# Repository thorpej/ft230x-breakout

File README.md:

# A Basic FTDI FT230X Breakout Board

This is a fairly straight-forward breakout board for the FTDI FT230X
USB UART.  The circuit is more-or-less the example bus-powered circuit
in the FT230X data sheet, and all of the I/O pins are simply brought
out to pin headers.  You can point them down for inserting into a breadboard,
or you can point them up for connecting with Dupont wires.  The board is
pretty small, so there are no mounting holes.

This work is licensed under the [Creative Commons Attribution
ShareAlike 4.0 International license](https://creativecommons.org/licenses/by-sa/4.0/).

At the time I designed this, the FT230X was the simplest of FTDI's USB UARTs.
It has *TXD*, *RXD*, *RTS*, and *CTS* serial signals, plus four general purpose
I/O pins that have several available functions (see the data sheet).  The
default configuration for two of those pins is to drive transmit and receive
LEDs, and so I went ahead and included those LEDs on the board along with
jumper headers to enable them.  If the jumpers are not installed, then the
two pins (*CB1* and *CB2*) are completely isolated from the LEDs, so they are
safe to use for whatever purpose you wish.

I designed and built this board mainly as a learning experience; I am planning
to use the FT230X in some other projects, and wanted to prove to myself that
I could do the necessary PCB layout and assembly work the part requires.  I'm
absolutely positive that better design is possible, but I'm just a hobbyist
with middle-aged-guy eyesight, so this is what you get!  :-)

## How to build it

With the exception of the pin headers, everything on this board is
surface-mount, so you will need to be comfortable with surface-mount
soldering.  The FT230XS is probably going to be the trickiest part to
solder, followed by the micro USB connector.  Both of those should be
fairly doable with both paste and hot air or drag soldering (and the
USB connector has through-holes for mounting).  There are lots of
surface-mount soldering tutorials on YouTube if you want to learn the
various techniques.

All of the surface-mount resistors, capacitors, and LEDs are in 0805 / 2012
packages.

Here are the parts you will need:

* One of the **ft230x-breakout** PCBs.  The Gerber files are provided here
and I have set up a shared project on PCBWay [here](XXX).
* 1 FT230XS USB UART IC in an SSOP-16 package (Mouser part number [**895-FT230XS-R**](https://www.mouser.com/ProductDetail/895-FT230XS-R)).
* 1 Molex 105017-0001 micro USB B connector (Mouser part number [**538-105017-0001**](https://www.mouser.com/ProductDetail/538-105017-0001)).
* 1 4.7uF tantalum capacitor (such as Mouser part number [**647-F951E475MPAAQ2**](https://www.mouser.com/ProductDetail/647-F951E475MPAAQ2)).
* 1 ferrite bead for HF noise suppression on the USB +5V rail.  I just used the
example part listed in the FT230X data sheet (Mouser part number [**875-MI0805K400R-10**](https://www.mouser.com/ProductDetail/875-MI0805K400R-10)).
* 2 100nF ceramic capacitors.
* 1 10nF ceramic capacitor.
* 2 47pF ceramic capacitors.
* 2 270 ohm 1/8W resistors.
* 2 27 ohm 1/8W resistors.
* 2 LEDs.  I like to use green for Tx (such as Mouser part numer [**710-150080GS75000**](https://www.mouser.com/ProductDetail/710-150080GS75000)) and red for
Rx (such as Mouser part numer [**710-150080RS75000**](https://www.mouser.com/ProductDetail/710-150080RS75000)).
* 2 standard 1x5 2.54mm pin headers for the signal connections.
* 2 standard 1x2 2.54mm pin headers and jumper caps for the LED enable jumpers.

A full reference of all components can be found in [ft230x-breakout-bom.pdf](ft230x-breakout-bom.pdf).

Solder the surface-mount parts before soldering the pin headers.  That's all
the assembly advice I'm going to give on this one!

If you have any questions about the board, you can reach out to me on
Twitter (*[@thorpej](https://twitter.com/thorpej)*) or Mastodon
(*[@thorpej@mastodon.sdf.org](https://mastodon.sdf.org/@thorpej)*).  You
can also check out my [YouTube channel](https://www.youtube.com/@thorpejsf),
which has this and other retrocomputing related content.

## Errata

### 1.0

* There is a silkscreen error: The Tx and Rx LED labels are swapped.  This
is corrected in revision 1.1.

## Changes

### 1.1

* Corrected the Tx and Rx LED labels on the front silkscreen.

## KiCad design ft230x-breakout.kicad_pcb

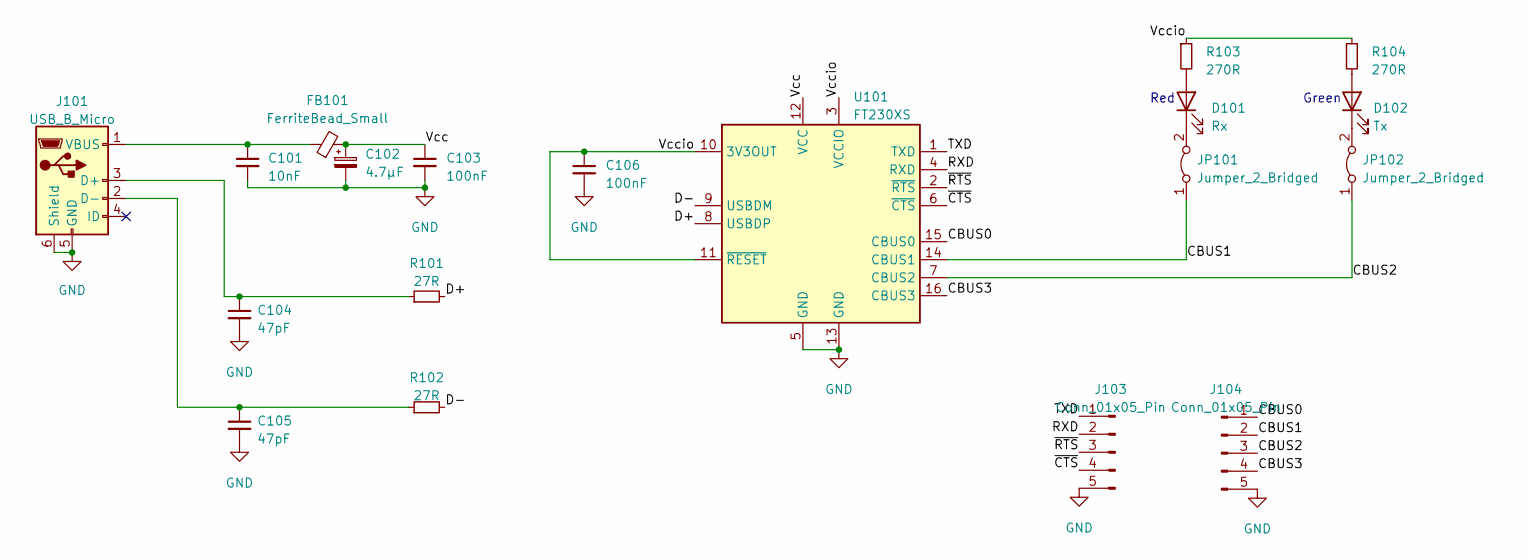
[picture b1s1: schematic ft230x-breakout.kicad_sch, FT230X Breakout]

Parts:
C101: 10nF; C_0805_2012Metric_Pad1.18x1.45mm_HandSolder
C102: 4.7µF; CP_EIA-2012-15_AVX-P_Pad1.30x1.05mm_HandSolder; Part Kyocera AVX F951E475MPAAQ2; Mouser 647-F951E475MPAAQ2
C103, C106: 100nF; C_0805_2012Metric_Pad1.18x1.45mm_HandSolder
C104, C105: 47pF; C_0805_2012Metric_Pad1.18x1.45mm_HandSolder
D101: Rx; LED_0805_2012Metric_Pad1.15x1.40mm_HandSolder; Part Wurth 150080GS75000; Mouser 710-150080GS75000
D102: Tx; LED_0805_2012Metric_Pad1.15x1.40mm_HandSolder; Part Wurth 150080RS75000; Mouser 710-150080RS75000
FB101: FerriteBead_Small; C_0805_2012Metric_Pad1.18x1.45mm_HandSolder; Part Laird MI0805K400R-10; Mouser 875-MI0805K400R-10
J101: USB_B_Micro; USB_Micro-B_Molex-105017-0001; Part Molex 105017-0001; Mouser 538-105017-0001
J103, J104: Conn_01x05_Pin; PinHeader_1x05_P2.54mm_Vertical
JP101, JP102: Jumper_2_Bridged; PinHeader_1x02_P2.54mm_Vertical
R101, R102: 27R; R_0805_2012Metric_Pad1.20x1.40mm_HandSolder
R103, R104: 270R; R_0805_2012Metric_Pad1.20x1.40mm_HandSolder
U101: FT230XS; SSOP-16_3.9x4.9mm_P0.635mm

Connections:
/CBUS0: J104.1, U101.15 (CBUS0)
/CBUS1: J104.2, JP101.1 (A), U101.14 (CBUS1)
/CBUS2: J104.3, JP102.1 (A), U101.7 (CBUS2)
/CBUS3: J104.4, U101.16 (CBUS3)
/D+: R101.2, U101.8 (USBDP)
/D-: R102.2, U101.9 (USBDM)
/RXD: J103.2, U101.4 (RXD)
/TXD: J103.1, U101.1 (TXD)
/Vcc: C102.1, C103.1, FB101.2, U101.12 (VCC)
/Vccio: C106.1, R103.1, R104.1, U101.3 (VCCIO), U101.10 (3V3OUT), U101.11 (~RESET)
/~CTS: J103.4, U101.6 (~CTS)
/~RTS: J103.3, U101.2 (~RTS)
GND: C101.2, C102.2, C103.2, C104.2, C105.2, C106.2, J101.5 (GND), J101.6 (Shield), J103.5, J104.5, U101.5 (GND), U101.13 (GND)
unnamed: D101.2 (A), R103.2
unnamed: D101.1 (K), JP101.2 (B)
unnamed: D102.2 (A), R104.2
unnamed: D102.1 (K), JP102.2 (B)
unnamed: C104.1, J101.3 (D+), R101.1
unnamed: C105.1, J101.2 (D-), R102.1
unnamed: C101.1, FB101.1, J101.1 (VBUS)

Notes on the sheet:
Red
Green

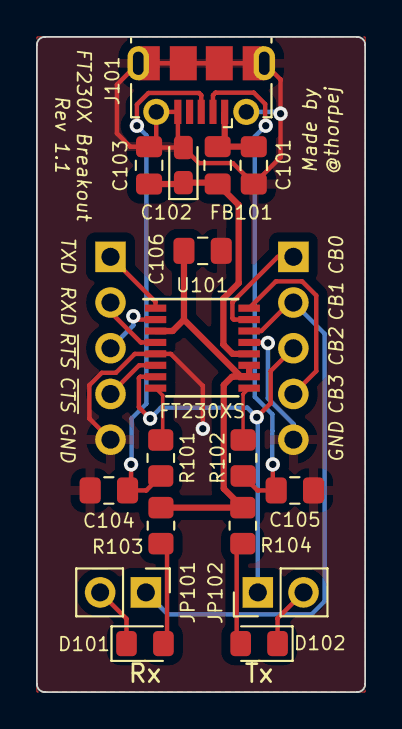
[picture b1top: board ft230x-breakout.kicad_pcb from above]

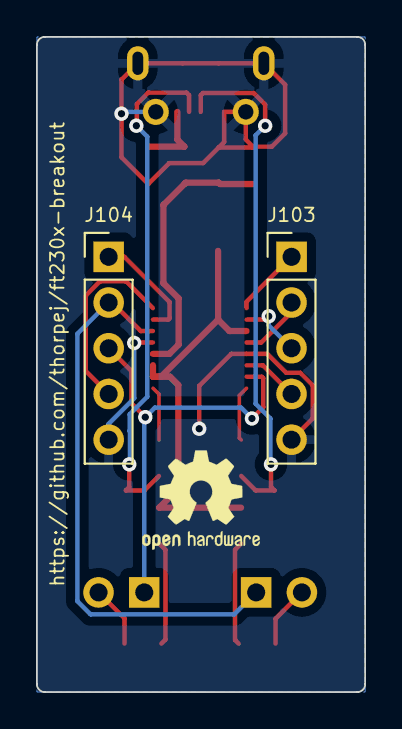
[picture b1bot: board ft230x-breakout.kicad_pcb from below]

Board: 2 copper layers, 18.2 x 36.4 mm, 19 parts (2 on the bottom side), 20 nets.

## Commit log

2024-07-03 A break-out board for the FTDI FT230XS. Circuit is largely based on the bus-powered example circuit from the FT230X data sheet. LEDs for Tx and Rx are included -- install jumpers to enable them (conn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
2024-07-03 Tweak some front silkscreen markings, and add GitHub URL to back silkscreen.
2024-07-03 Generate Gerbers.
2024-07-04 Put some meat into the README.
2024-07-04 Add LICENSE.
2024-07-04 Fix some typos and omissions.
2024-07-05 Correct a silkscreen problem on rev 1.0 of the board: Tx and Rx LED labels were swapped. Bump rev to 1.1.
2024-07-05 Slight formatting tweak.
2024-07-05 Another formatting tweak.

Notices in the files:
README.md:
CC BY-SA 4.0
ft230x-breakout.kicad_pcb:
Copyright (c) 2024 Jason R. Thorpe.  See LICENSE.
